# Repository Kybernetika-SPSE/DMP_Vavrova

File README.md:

# DMP_Vavrova
Maturitní práce - Autíčko na sledování čáry

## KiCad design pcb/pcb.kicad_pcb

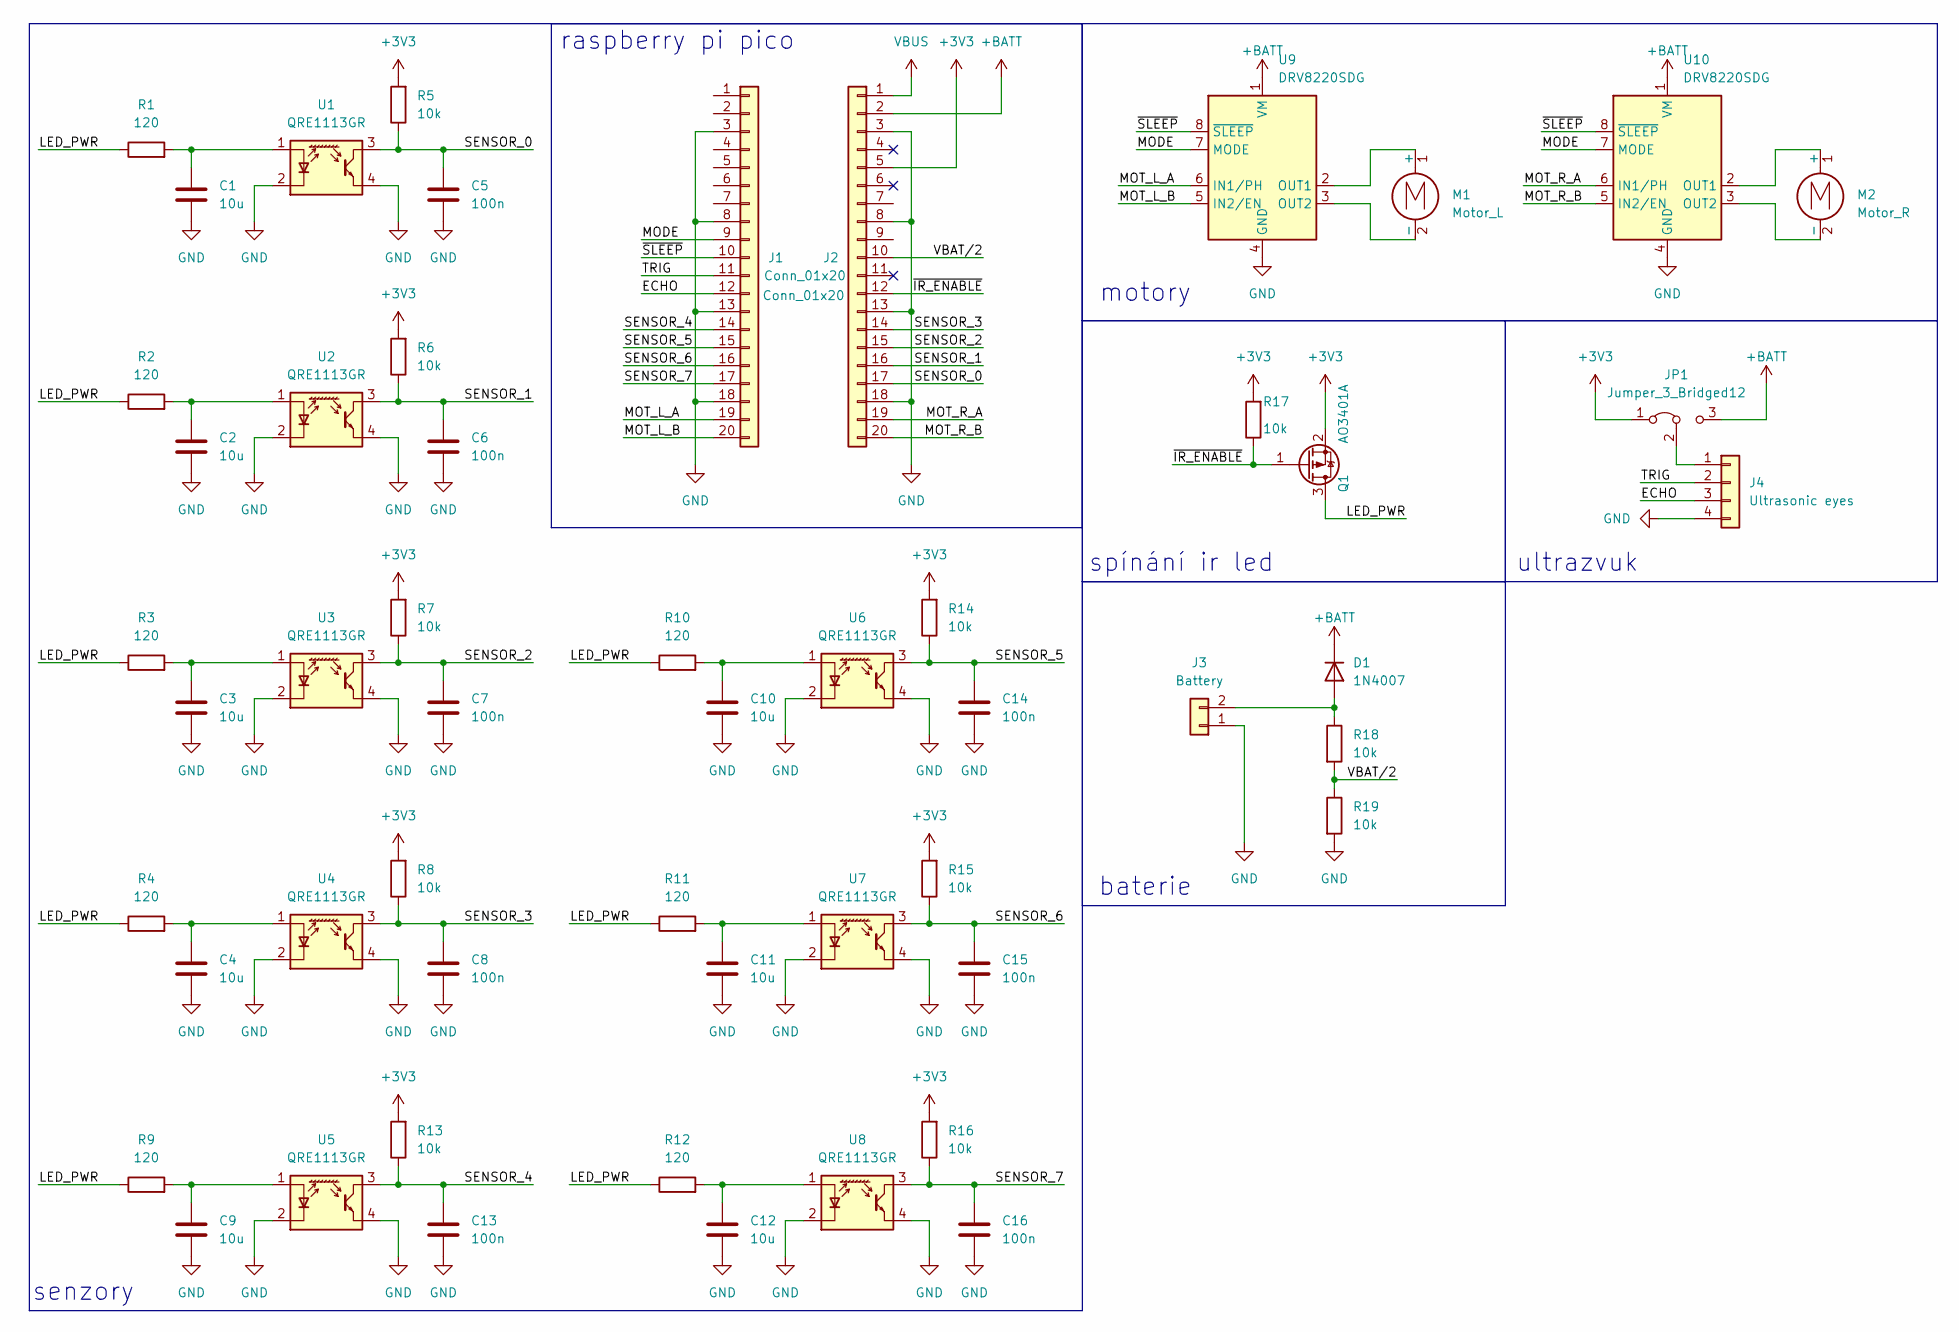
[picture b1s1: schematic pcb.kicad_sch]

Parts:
C1, C2, C3, C4, C9, C10, C11, C12: 10u; C_0603_1608Metric_Pad1.08x0.95mm_HandSolder
C5, C6, C7, C8, C13, C14, C15, C16: 100n; C_0603_1608Metric_Pad1.08x0.95mm_HandSolder
D1: 1N4007; D_A-405_P10.16mm_Horizontal
J1, J2: Conn_01x20; PinSocket_1x20_P2.54mm_Vertical
J3: Battery; BATTERY-SMD_18650-1S-L77.1-W20.7-1
J4: Ultrasonic eyes; PinSocket_1x04_P2.54mm_Vertical
JP1: Jumper_3_Bridged12; PinHeader_1x03_P2.54mm_Vertical
M1: Motor_L; JST_XH_B2B-XH-A_1x02_P2.50mm_Vertical
M2: Motor_R; JST_XH_B2B-XH-A_1x02_P2.50mm_Vertical
Q1: AO3401A; SOT-23; LCSC C2938367
R1, R2, R3, R4, R9, R10, R11, R12: 120; R_0603_1608Metric_Pad0.98x0.95mm_HandSolder
R5, R6, R7, R8, R13, R14, R15, R16, R18, R19: 10k; R_0603_1608Metric_Pad0.98x0.95mm_HandSolder
R17: 10k; R_0603_1608Metric; LCSC C25744
U1, U2, U3, U4, U5, U6, U7, U8: QRE1113GR; OnSemi_CASE100CY
U9, U10: DRV8220SDG; WSON-8-1EP_2x2mm_P0.5mm_EP0.9x1.6mm

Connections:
+3V3: J2.5, JP1.1 (A), Q1.2 (S), R5.2, R6.2, R7.2, R8.2, R13.2, R14.2, R15.2, R16.2, R17.2
+BATT: D1.1 (K), J2.2, JP1.3 (B), U9.1 (VM), U10.1 (VM)
/ECHO: J1.12, J4.3
/LED_PWR: Q1.3 (D), R1.1, R2.1, R3.1, R4.1, R9.1, R10.1, R11.1, R12.1
/MODE: J1.9, U9.7 (MODE), U10.7 (MODE)
/MOT_L_A: J1.19, U9.6 (IN1/PH)
/MOT_L_B: J1.20, U9.5 (IN2/EN)
/MOT_R_A: J2.19, U10.6 (IN1/PH)
/MOT_R_B: J2.20, U10.5 (IN2/EN)
/SENSOR_0: C5.1, J2.17, R5.1, U1.3
/SENSOR_1: C6.1, J2.16, R6.1, U2.3
/SENSOR_2: C7.1, J2.15, R7.1, U3.3
/SENSOR_3: C8.1, J2.14, R8.1, U4.3
/SENSOR_4: C13.1, J1.14, R13.1, U5.3
/SENSOR_5: C14.1, J1.15, R14.1, U6.3
/SENSOR_6: C15.1, J1.16, R15.1, U7.3
/SENSOR_7: C16.1, J1.17, R16.1, U8.3
/TRIG: J1.11, J4.2
/VBAT/2: J2.10, R18.2, R19.1
/~IR_ENABLE: J2.12, Q1.1 (G), R17.1
/~SLEEP: J1.10, U9.8 (~SLEEP), U10.8 (~SLEEP)
GND: C1.2, C2.2, C3.2, C4.2, C5.2, C6.2, C7.2, C8.2, C9.2, C10.2, C11.2, C12.2, C13.2, C14.2, C15.2, C16.2, J1.3, J1.8, J1.13, J1.18, J2.3, J2.8, J2.13, J2.18, J3.1, J4.4, R19.2, U1.2 (K), U1.4, U2.2 (K), U2.4, U3.2 (K), U3.4, U4.2 (K), U4.4, U5.2 (K), U5.4, U6.2 (K), U6.4, U7.2 (K), U7.4, U8.2 (K), U8.4, U9.4 (GND), U9.9 (GND), U10.4 (GND), U10.9 (GND)
unnamed: D1.2 (A), J3.2, R18.1
unnamed: J4.1, JP1.2 (C)
unnamed: M1.1 (+), U9.2 (OUT1)
unnamed: M1.2 (-), U9.3 (OUT2)
unnamed: M2.1 (+), U10.2 (OUT1)
unnamed: M2.2 (-), U10.3 (OUT2)
unnamed: C1.1, R1.2, U1.1 (A)
unnamed: C2.1, R2.2, U2.1 (A)
unnamed: C3.1, R3.2, U3.1 (A)
unnamed: C4.1, R4.2, U4.1 (A)
unnamed: C9.1, R9.2, U5.1 (A)
unnamed: C10.1, R10.2, U6.1 (A)
unnamed: C11.1, R11.2, U7.1 (A)
unnamed: C12.1, R12.2, U8.1 (A)
VBUS: J2.1

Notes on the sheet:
baterie
ultrazvuk
raspberry pi pico
senzory
spínání ir led
motory

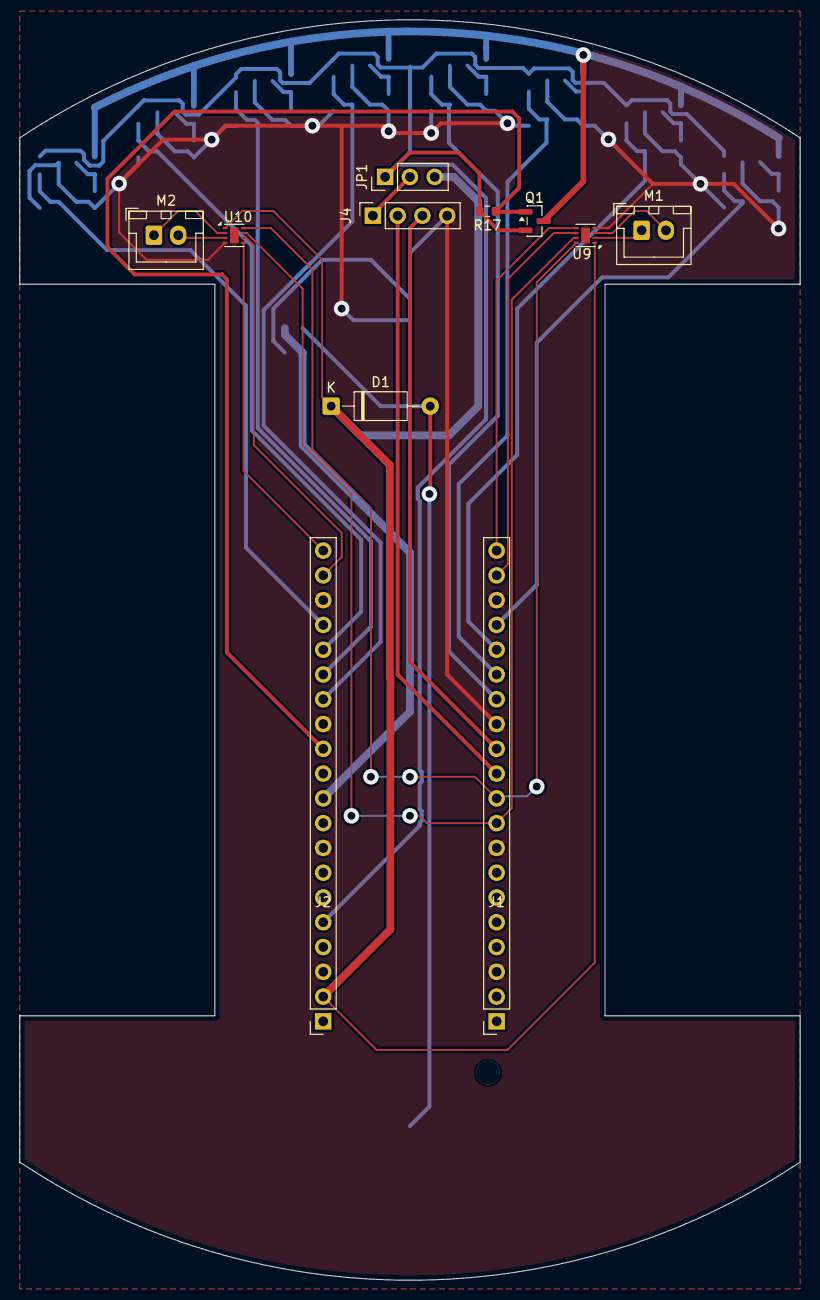
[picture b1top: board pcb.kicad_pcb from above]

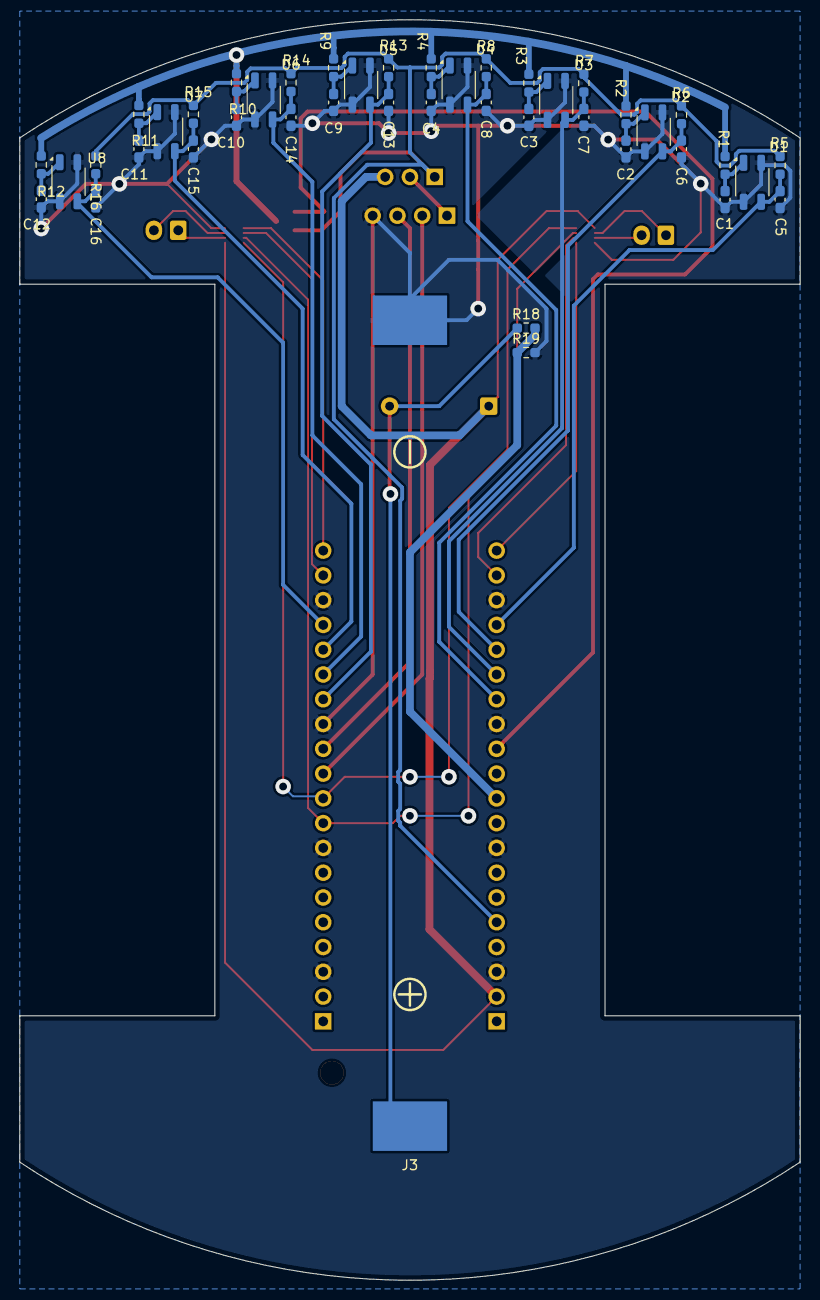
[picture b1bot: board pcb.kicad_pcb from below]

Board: 2 copper layers, 80.0 x 129.2 mm, 54 parts (43 on the bottom side), 36 nets.

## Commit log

2026-01-17 non final - only partly done scheme
2026-01-20 pridano par veci
2026-01-22 schéma
2026-01-26 schéma začátek pcb1
2026-02-17 update tempotary
2026-02-18 Úpravy pro zjednodušení
2026-02-18 Úklid schématu
2026-02-20 Fix schematu #1
2026-02-20 Fix schématu #2
2026-02-24 pcb2
2026-02-25 Zapojení senzorů
2026-02-25 Dodělané pcb
2026-02-26 pcb upravená cestička
